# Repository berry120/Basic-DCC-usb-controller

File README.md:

# Basic DCC USB controller

Note - This is a fairly old project (2015) that I've uploaded to Github much more recently. Consists of a board schematic & layout, and firmware (Arduino based) for the ATMega328.

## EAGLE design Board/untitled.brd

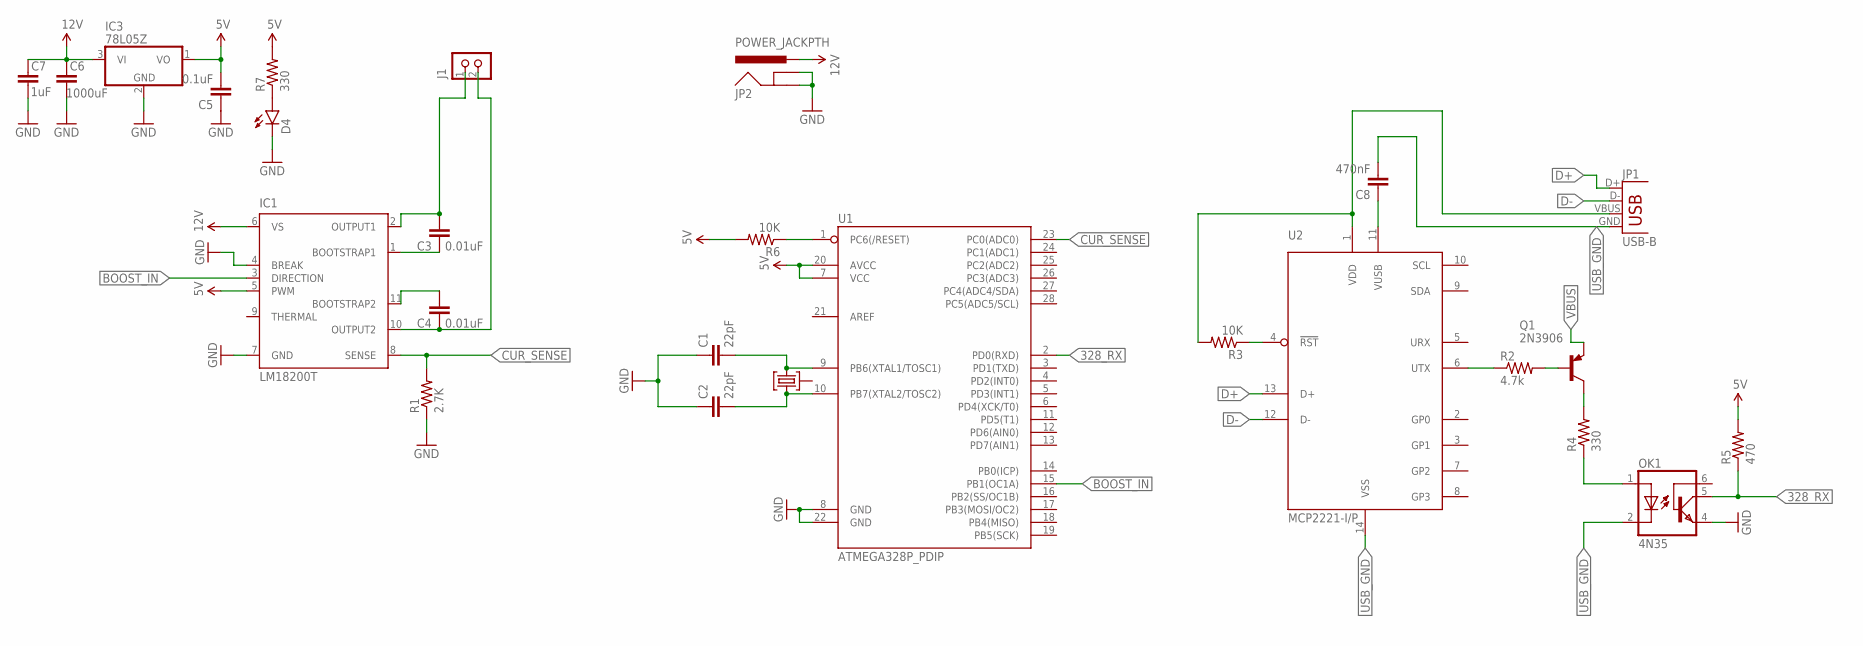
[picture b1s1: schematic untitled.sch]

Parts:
C1, C2: 22pF; CAP-PTH-SMALLEZ; MPN DEC1X3J220JC4B
C3, C4: 0.01uF; CAP-PTH-SMALLEZ; MPN D103K43Y5PH63L2R
C5: 0.1uF; CAP-PTH-SMALLEZ; MPN MCRH100V104M5X11
C6: 1000uF; CAP-PTH-SMALLEZ; MPN MCGPR10V108M8X14
C7: 1uF; CAP-PTH-SMALLEZ; MPN MCNP16V105M5X11
C8: 470nF; CAP-PTH-SMALLEZ; MPN MCBU5471K5
D4: LED-3MM-NO_SILK; LED3MM-NS; MPN MCL034MD
IC1: LM18200T; TO-220-11; MPN LMD18200T/NOPB
IC3: 78L05Z; TO92; MPN L78L05ACZ
J1: CON_TERMINAL_BLOCK_02-5MM; TERMINAL_BLOCK_2P_5; MPN CTB0102/2
JP1: USB-B; USB-B-PTH; MPN USB-B-S-RA.
JP2: POWER_JACKPTH; POWER_JACK_PTH; MPN DC10A
OK1: 4N35; DIL06
Q1: 2N3906; TO92; MPN 2N3906
QF1: 8M10AHC49T; HC49U; MPN 16.000MHZ HC49/4H/30/50/40/18PF/ATF
R1: 2.7K; AXIAL-0.3; MPN MCRE000042
R2: 4.7k; AXIAL-0.3; MPN MCRE000045
R3, R6: 10K; AXIAL-0.3; MPN MCMF006FF1002A50
R4, R7: 330; AXIAL-0.3; MPN MCRE000031
R5: 470; AXIAL-0.3; MPN MCRE000033
U1: ATMEGA328P_PDIP; DIL28-3; MPN ATMEGA328P-PU
U2: MCP2221-I/P; DIL14; MPN MCP2221-I/P

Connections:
5V: C5.2, IC1.5 (PWM), IC3.1 (VO), R5.P$2 (2), R6.P$2 (2), R7.P$2 (2), U1.7 (VCC), U1.20 (AVCC)
12V: C6.2, C7.2, IC1.6 (VS), IC3.3 (VI), JP2.PWR
328_RX: OK1.5 (COL), R5.P$1 (1), U1.2 (PD0(RXD))
BOOST_IN: IC1.3 (DIRECTION), U1.15 (PB1(OC1A))
CUR_SENSE: IC1.8 (SENSE), R1.P$2 (2), U1.23 (PC0(ADC0))
D+: JP1.D+, U2.13 (D+)
D-: JP1.D-, U2.12 (D-)
GND: C1.1, C2.1, C5.1, C6.1, C7.1, D4.K (C), IC1.4 (BREAK), IC1.7 (GND), IC3.2 (GND), JP2.GND, JP2.GNDBREAK, OK1.4 (EMI), R1.P$1 (1), U1.8 (GND), U1.22 (GND)
unnamed: Q1.1 (C), R4.P$2 (2)
unnamed: C3.1, IC1.1 (BOOTSTRAP1)
unnamed: C8.1, U2.11 (VUSB)
unnamed: C4.2, IC1.11 (BOOTSTRAP2)
unnamed: R3.P$1 (1), U2.4 (!RST)
unnamed: R2.P$1 (1), U2.6 (UTX)
unnamed: Q1.2 (B), R2.P$2 (2)
unnamed: OK1.1 (A), R4.P$1 (1)
unnamed: C1.2, QF1.3, U1.9 (PB6(XTAL1/TOSC1))
unnamed: C2.2, QF1.1, U1.10 (PB7(XTAL2/TOSC2))
unnamed: R6.P$1 (1), U1.1 (PC6(/RESET))
unnamed: D4.A, R7.P$1 (1)
TRACK_1: C3.2, IC1.2 (OUTPUT1), J1.1
TRACK_2: C4.1, IC1.10 (OUTPUT2), J1.2
USB_GND: C8.2, JP1.GND, OK1.2 (C), U2.14 (VSS)
VBUS: JP1.VBUS, Q1.3 (E), R3.P$2 (2), U2.1 (VDD)

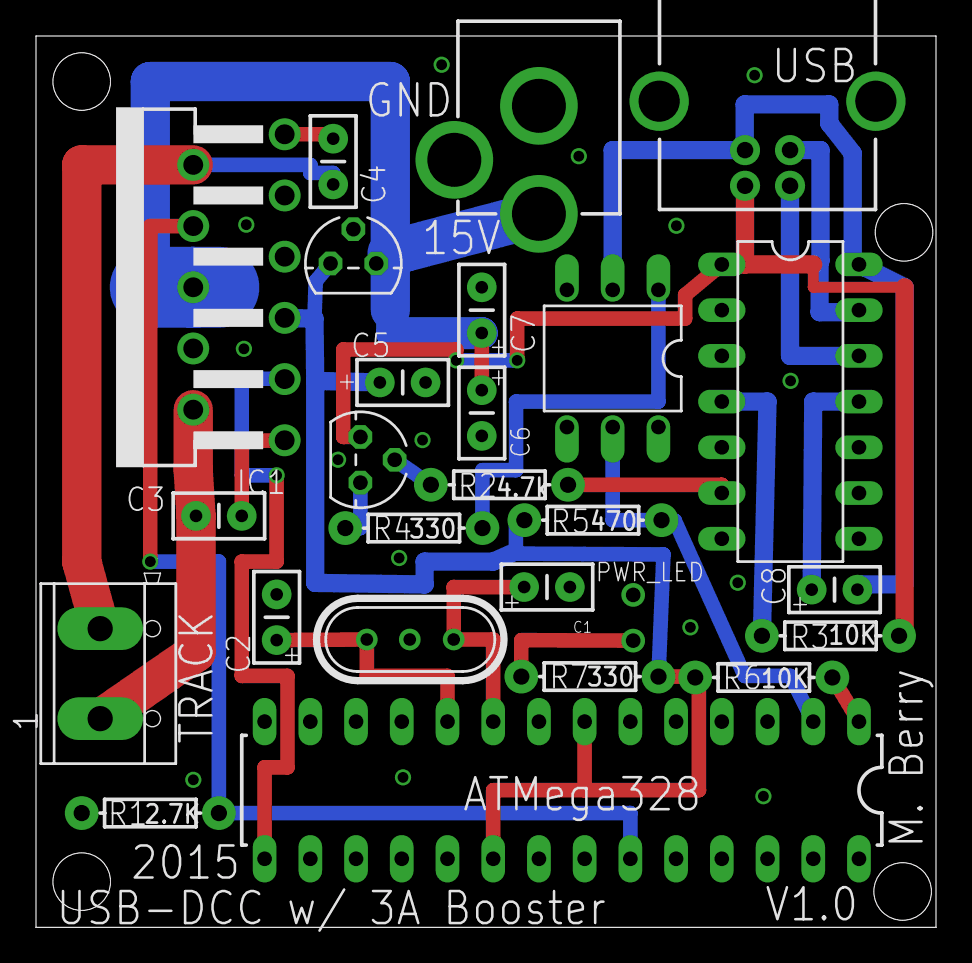
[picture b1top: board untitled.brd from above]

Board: 2 copper layers, 50.0 x 49.5 mm, 26 parts (0 on the bottom side), 24 nets.

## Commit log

2019-07-21 Add board and firmware

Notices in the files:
parts and their libraries:
SparkFun-Capacitors: Licensing: Creative Commons ShareAlike 4.0 International - https://creativecommons.org/licenses/by-sa/4.0
